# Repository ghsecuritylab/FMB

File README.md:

master only for working parts
work branch for incompltele/inprogress parts

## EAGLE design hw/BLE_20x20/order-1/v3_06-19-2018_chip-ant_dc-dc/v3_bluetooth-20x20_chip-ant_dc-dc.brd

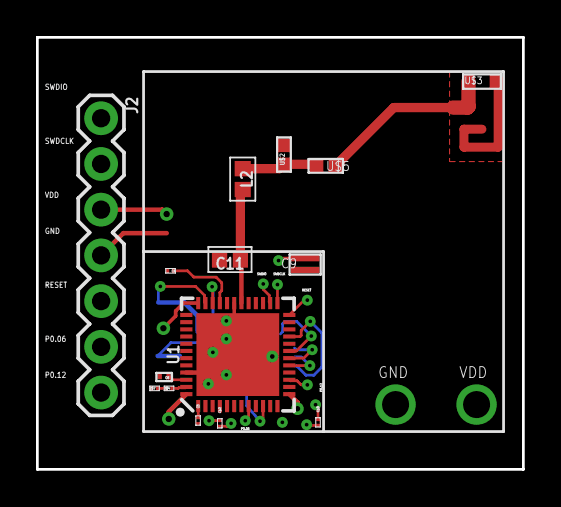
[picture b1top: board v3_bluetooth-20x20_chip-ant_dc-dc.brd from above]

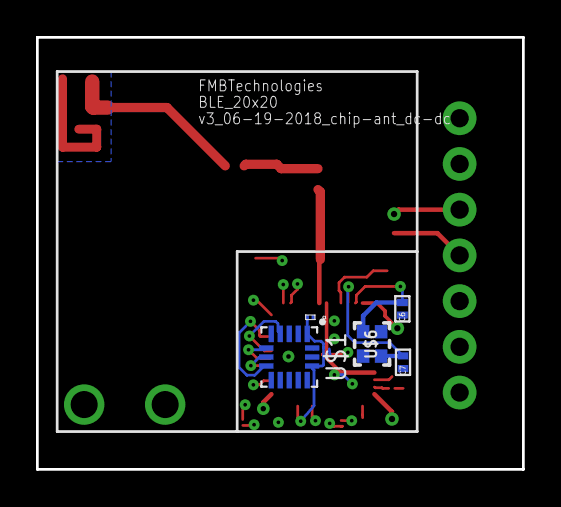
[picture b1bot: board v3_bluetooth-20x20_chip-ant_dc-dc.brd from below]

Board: 4 copper layers, 27.0 x 24.0 mm, 20 parts (5 on the bottom side), 22 nets.

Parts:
C1, C3, C10, C12: C0402X5R0G104M020BCCAP_0402-L; CAP_0402-L
C4: C0402C0G1C101J020BCCAP_0402-L; CAP_0402-L
C6, C7: GRM1555C1H6R0CA01D; CAPC1005X55N
C8: GRMMDXR60J105ME05D; CAPC0502X28N
C9: 4P7UFCAPACITOR4P7UFCAPACITOR; 4P7UFCAPACITOR
C11: 0.8pF; 0402
J2: header; 1X07
L2: 3.9nH; 0402
U1: NRF52832; QFN48-6X6MM
U$1: ADXL362; TFLGA-16/3.3MMX3.1MM
U$2: TUNINGINDUCTOR; 0402
U$3: 2450AT14A0100
U$4, U$7: INDUCTOR; 0402
U$5: 0402-1005
U$6: 32MHZCRYSTAL

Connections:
ADXL_POWER-QFAA: C1.2, U1.10, U$1.VDD/IO, U$1.VS
ANT-QFAA: C11.2, L2.1, U1.30
CS-QFAA: U1.21, U$1.CS
DEC1-QFAA: C3.1, U1.1
DEC3-QFAA: C4.1, U1.33
DEC4-QFAA: C8.1, U1.46
GND: C1.1, C3.2, C4.2, C6.1, C7.1, C8.2, C9.1, C10.1, C11.1, C12.1, J2.4, U1.31, U1.45, U1.EP, U$1.GND@1, U$1.GND@2, U$1.GND@3, U$2.2, U$7.1
MISO-QFAA: U1.17, U$1.MISO
MOSI-QFAA: U1.18, U$1.MOSI
unnamed: L2.2, U$2.1, U$5.2
unnamed: U$3.FEED, U$5.1
unnamed: U1.47, U$4.2
unnamed: U$4.1, U$7.2
P0.06-QFAA: J2.6, U1.8
P0.12-QFAA: J2.7, U1.15
RESET-QFAA: J2.5, U1.24
SCLK-QFAA: U1.19, U$1.SCLK
SWDCLK-QFAA: J2.2, U1.25
SWDIO-QFAA: J2.1, U1.26
VDD: C9.2, C10.2, C12.2, J2.3, U1.13, U1.36, U1.48
XC1-QFAA: C7.2, U1.34, U$6.1
XC2-QFAA: C6.2, U1.35, U$6.3

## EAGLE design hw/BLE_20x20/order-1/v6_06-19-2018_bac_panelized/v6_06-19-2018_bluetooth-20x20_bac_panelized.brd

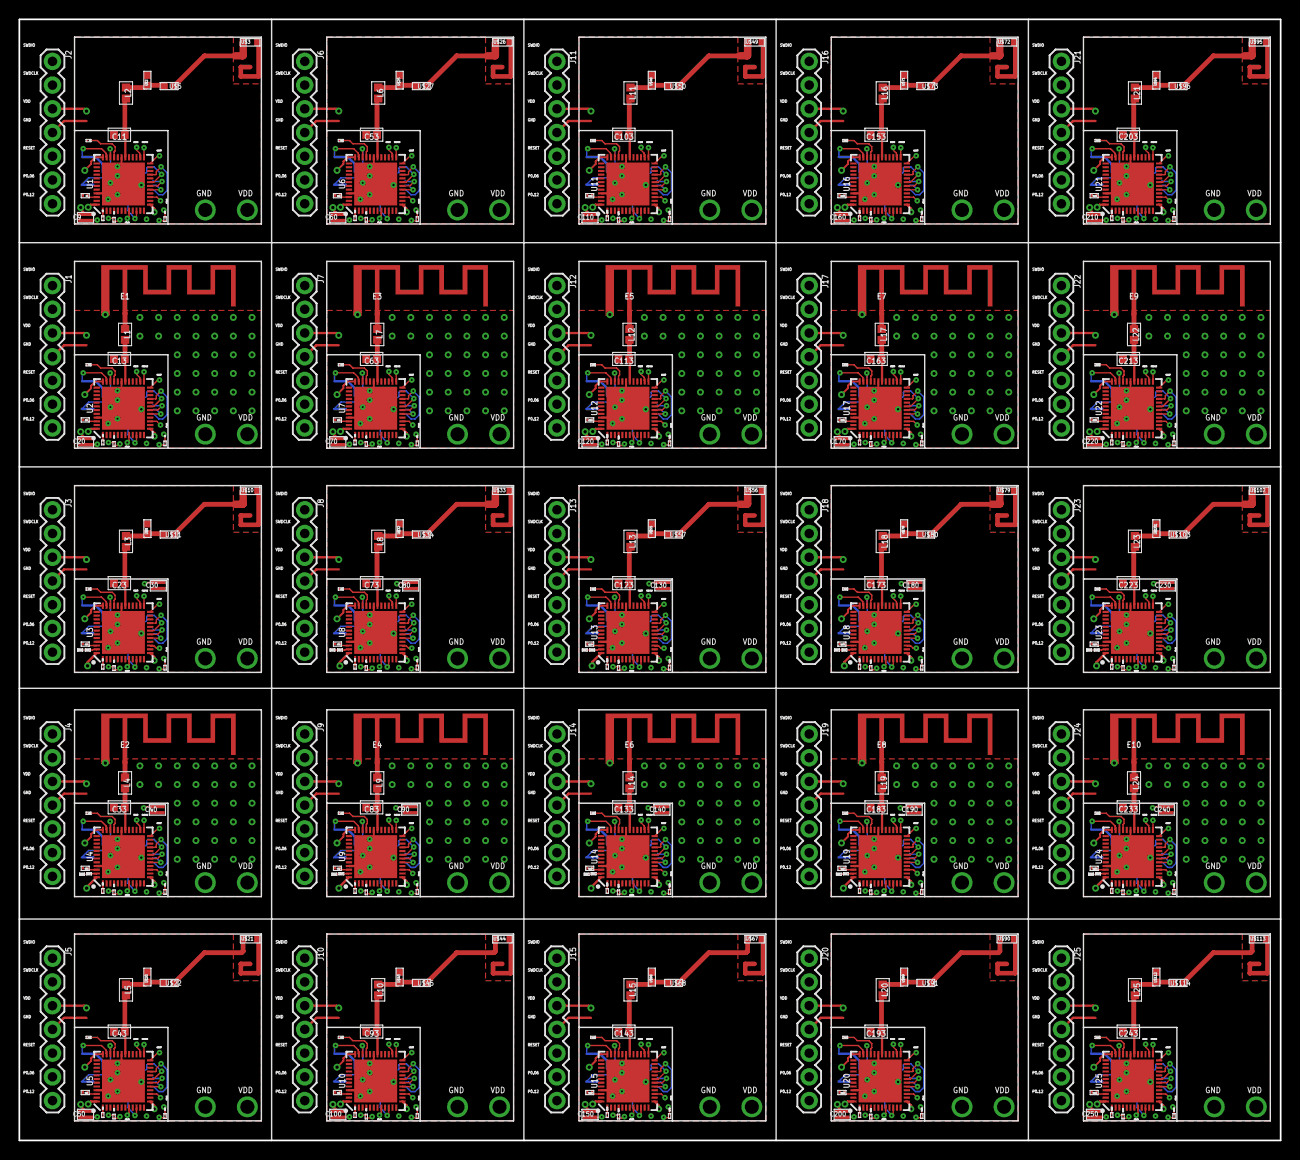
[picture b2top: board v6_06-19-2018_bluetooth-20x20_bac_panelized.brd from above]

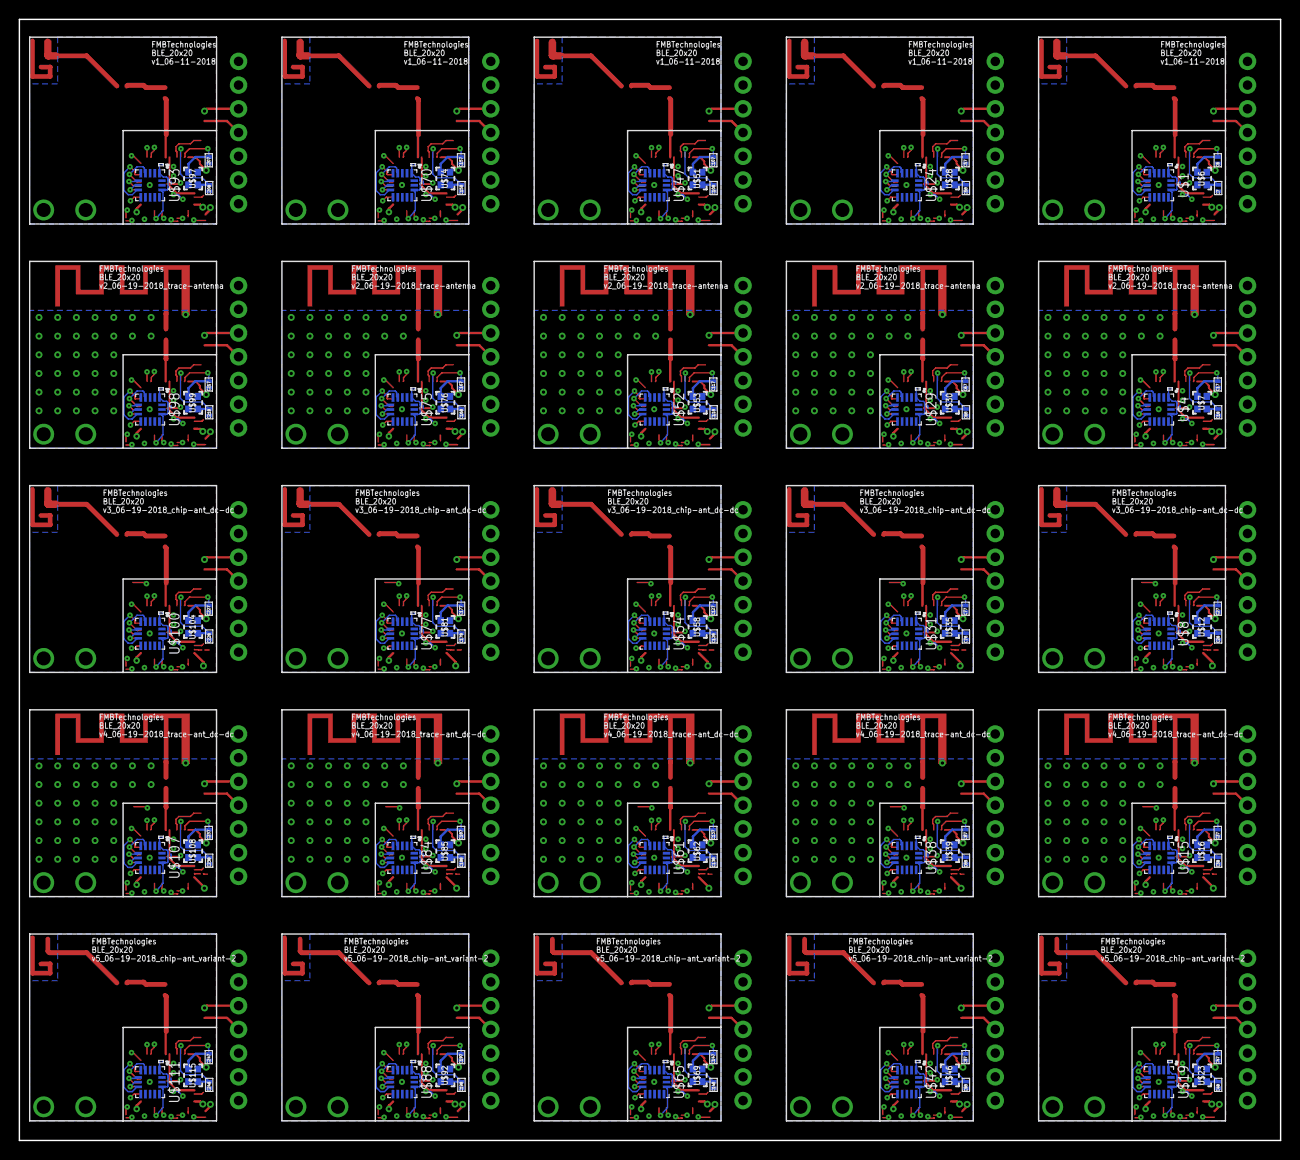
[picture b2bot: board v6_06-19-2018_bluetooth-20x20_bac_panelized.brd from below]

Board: 4 copper layers, 135.0 x 120.0 mm, 450 parts (125 on the bottom side), 510 nets.

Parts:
C1, C2, C3, C5, C10, C12, C14, C15, C21, C22, C24, C25, C31, C32, C34, C35, C41, C42, C44, C45, C51, C52, C54, C55, C61, C62, C64, C65, C71, C72, C74, C75, C81, C82, C84, C85, C91, C92, C94, C95, C101, C102, C104, C105, C111, C112, C114, C115, C121, C122, C124, C125, C131, C132, C134, C135, C141, C142, C144, C145, C151, C152, C154, C155, C161, C162, C164, C165, C171, C172, C174, C175, C181, C182, C184, C185, C191, C192, C194, C195, C201, C202, C204, C205, C211, C212, C214, C215, C221, C222, C224, C225, C231, C232, C234, C235, C241, C242, C244, C245: C0402X5R0G104M020BCCAP_0402-L; CAP_0402-L
C4, C16, C26, C36, C46, C56, C66, C76, C86, C96, C106, C116, C126, C136, C146, C156, C166, C176, C186, C196, C206, C216, C226, C236, C246: C0402C0G1C101J020BCCAP_0402-L; CAP_0402-L
C6, C7, C17, C18, C27, C28, C37, C38, C47, C48, C57, C58, C67, C68, C77, C78, C87, C88, C97, C98, C107, C108, C117, C118, C127, C128, C137, C138, C147, C148, C157, C158, C167, C168, C177, C178, C187, C188, C197, C198, C207, C208, C217, C218, C227, C228, C237, C238, C247, C248: GRM1555C1H6R0CA01D; CAPC1005X55N
C8, C19, C29, C39, C49, C59, C69, C79, C89, C99, C109, C119, C129, C139, C149, C159, C169, C179, C189, C199, C209, C219, C229, C239, C249: GRMMDXR60J105ME05D; CAPC0502X28N
C9, C20, C30, C40, C50, C60, C70, C80, C90, C100, C110, C120, C130, C140, C150, C160, C170, C180, C190, C200, C210, C220, C230, C240, C250: 4P7UFCAPACITOR4P7UFCAPACITOR; 4P7UFCAPACITOR
C11, C13, C23, C33, C43, C53, C63, C73, C83, C93, C103, C113, C123, C133, C143, C153, C163, C173, C183, C193, C203, C213, C223, C233, C243: 0.8pF; 0402
E1, E2, E3, E4, E5, E6, E7, E8, E9, E10: ANT; TRACE_ANTENNA_2.4GHZ_15.2MM
J1, J2, J3, J4, J5, J6, J7, J8, J9, J10, J11, J12, J13, J14, J15, J16, J17, J18, J19, J20, J21, J22, J23, J24, J25: header; 1X07
L1, L2, L3, L4, L5, L6, L7, L8, L9, L10, L11, L12, L13, L14, L15, L16, L17, L18, L19, L20, L21, L22, L23, L24, L25: 3.9nH; 0402
U1, U2, U3, U4, U5, U6, U7, U8, U9, U10, U11, U12, U13, U14, U15, U16, U17, U18, U19, U20, U21, U22, U23, U24, U25: NRF52832; QFN48-6X6MM
U$1, U$4, U$8, U$15, U$19, U$24, U$29, U$31, U$38, U$42, U$47, U$52, U$54, U$61, U$65, U$70, U$75, U$77, U$84, U$88, U$93, U$98, U$100, U$107, U$111: ADXL362; TFLGA-16/3.3MMX3.1MM
U$2, U$9, U$20, U$25, U$32, U$43, U$48, U$55, U$66, U$71, U$78, U$89, U$94, U$101, U$112: TUNINGINDUCTOR; 0402
U$3, U$10, U$21, U$26, U$33, U$44, U$49, U$56, U$67, U$72, U$79, U$90, U$95, U$102, U$113: 2450AT14A0100
U$5, U$11, U$22, U$27, U$34, U$45, U$50, U$57, U$68, U$73, U$80, U$91, U$96, U$103, U$114: 0402-1005
U$6, U$7, U$12, U$16, U$23, U$28, U$30, U$35, U$39, U$46, U$51, U$53, U$58, U$62, U$69, U$74, U$76, U$81, U$85, U$92, U$97, U$99, U$104, U$108, U$115: 32MHZCRYSTAL
U$13, U$14, U$17, U$18, U$36, U$37, U$40, U$41, U$59, U$60, U$63, U$64, U$82, U$83, U$86, U$87, U$105, U$106, U$109, U$110: INDUCTOR; 0402

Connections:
ADXL_POWER-QFAA: C1.2, U1.10, U$1.VDD/IO, U$1.VS
ADXL_POWER-QFAA1: C2.2, U2.10, U$4.VDD/IO, U$4.VS
ADXL_POWER-QFAA2: C21.2, U3.10, U$8.VDD/IO, U$8.VS
ADXL_POWER-QFAA3: C31.2, U4.10, U$15.VDD/IO, U$15.VS
ADXL_POWER-QFAA4: C41.2, U5.10, U$19.VDD/IO, U$19.VS
ADXL_POWER-QFAA5: C51.2, U6.10, U$24.VDD/IO, U$24.VS
ADXL_POWER-QFAA6: C61.2, U7.10, U$29.VDD/IO, U$29.VS
ADXL_POWER-QFAA7: C71.2, U8.10, U$31.VDD/IO, U$31.VS
ADXL_POWER-QFAA8: C81.2, U9.10, U$38.VDD/IO, U$38.VS
ADXL_POWER-QFAA9: C91.2, U10.10, U$42.VDD/IO, U$42.VS
ADXL_POWER-QFAA10: C101.2, U11.10, U$47.VDD/IO, U$47.VS
ADXL_POWER-QFAA11: C111.2, U12.10, U$52.VDD/IO, U$52.VS
ADXL_POWER-QFAA12: C121.2, U13.10, U$54.VDD/IO, U$54.VS
ADXL_POWER-QFAA13: C131.2, U14.10, U$61.VDD/IO, U$61.VS
ADXL_POWER-QFAA14: C141.2, U15.10, U$65.VDD/IO, U$65.VS
ADXL_POWER-QFAA15: C151.2, U16.10, U$70.VDD/IO, U$70.VS
ADXL_POWER-QFAA16: C161.2, U17.10, U$75.VDD/IO, U$75.VS
ADXL_POWER-QFAA17: C171.2, U18.10, U$77.VDD/IO, U$77.VS
ADXL_POWER-QFAA18: C181.2, U19.10, U$84.VDD/IO, U$84.VS
ADXL_POWER-QFAA19: C191.2, U20.10, U$88.VDD/IO, U$88.VS
ADXL_POWER-QFAA20: C201.2, U21.10, U$93.VDD/IO, U$93.VS
ADXL_POWER-QFAA21: C211.2, U22.10, U$98.VDD/IO, U$98.VS
ADXL_POWER-QFAA22: C221.2, U23.10, U$100.VDD/IO, U$100.VS
ADXL_POWER-QFAA23: C231.2, U24.10, U$107.VDD/IO, U$107.VS
ADXL_POWER-QFAA24: C241.2, U25.10, U$111.VDD/IO, U$111.VS
ANT-QFAA: C11.2, L2.1, U1.30
ANT-QFAA1: C13.2, L1.1, U2.30
ANT-QFAA2: C23.2, L3.1, U3.30
ANT-QFAA3: C33.2, L4.1, U4.30
ANT-QFAA4: C43.2, L5.1, U5.30
ANT-QFAA5: C53.2, L6.1, U6.30
ANT-QFAA6: C63.2, L7.1, U7.30
ANT-QFAA7: C73.2, L8.1, U8.30
ANT-QFAA8: C83.2, L9.1, U9.30
ANT-QFAA9: C93.2, L10.1, U10.30
ANT-QFAA10: C103.2, L11.1, U11.30
ANT-QFAA11: C113.2, L12.1, U12.30
ANT-QFAA12: C123.2, L13.1, U13.30
ANT-QFAA13: C133.2, L14.1, U14.30
ANT-QFAA14: C143.2, L15.1, U15.30
ANT-QFAA15: C153.2, L16.1, U16.30
ANT-QFAA16: C163.2, L17.1, U17.30
ANT-QFAA17: C173.2, L18.1, U18.30
ANT-QFAA18: C183.2, L19.1, U19.30
ANT-QFAA19: C193.2, L20.1, U20.30
ANT-QFAA20: C203.2, L21.1, U21.30
ANT-QFAA21: C213.2, L22.1, U22.30
ANT-QFAA22: C223.2, L23.1, U23.30
ANT-QFAA23: C233.2, L24.1, U24.30
ANT-QFAA24: C243.2, L25.1, U25.30
CS-QFAA: U1.21, U$1.CS
CS-QFAA1: U2.21, U$4.CS
CS-QFAA2: U3.21, U$8.CS
CS-QFAA3: U4.21, U$15.CS
CS-QFAA4: U5.21, U$19.CS
CS-QFAA5: U6.21, U$24.CS
CS-QFAA6: U7.21, U$29.CS
CS-QFAA7: U8.21, U$31.CS
CS-QFAA8: U9.21, U$38.CS
CS-QFAA9: U10.21, U$42.CS
CS-QFAA10: U11.21, U$47.CS
CS-QFAA11: U12.21, U$52.CS
CS-QFAA12: U13.21, U$54.CS
CS-QFAA13: U14.21, U$61.CS
CS-QFAA14: U15.21, U$65.CS
CS-QFAA15: U16.21, U$70.CS
CS-QFAA16: U17.21, U$75.CS
CS-QFAA17: U18.21, U$77.CS
CS-QFAA18: U19.21, U$84.CS
CS-QFAA19: U20.21, U$88.CS
CS-QFAA20: U21.21, U$93.CS
CS-QFAA21: U22.21, U$98.CS
CS-QFAA22: U23.21, U$100.CS
CS-QFAA23: U24.21, U$107.CS
CS-QFAA24: U25.21, U$111.CS
DEC1-QFAA: C3.1, U1.1
DEC1-QFAA1: C15.1, U2.1
DEC1-QFAA2: C25.1, U3.1
DEC1-QFAA3: C35.1, U4.1
DEC1-QFAA4: C45.1, U5.1
DEC1-QFAA5: C55.1, U6.1
DEC1-QFAA6: C65.1, U7.1
DEC1-QFAA7: C75.1, U8.1
DEC1-QFAA8: C85.1, U9.1
DEC1-QFAA9: C95.1, U10.1
DEC1-QFAA10: C105.1, U11.1
DEC1-QFAA11: C115.1, U12.1
DEC1-QFAA12: C125.1, U13.1
DEC1-QFAA13: C135.1, U14.1
DEC1-QFAA14: C145.1, U15.1
DEC1-QFAA15: C155.1, U16.1
DEC1-QFAA16: C165.1, U17.1
DEC1-QFAA17: C175.1, U18.1
DEC1-QFAA18: C185.1, U19.1
DEC1-QFAA19: C195.1, U20.1
DEC1-QFAA20: C205.1, U21.1
DEC1-QFAA21: C215.1, U22.1
DEC1-QFAA22: C225.1, U23.1
DEC1-QFAA23: C235.1, U24.1
DEC1-QFAA24: C245.1, U25.1
DEC3-QFAA: C4.1, U1.33
DEC3-QFAA1: C16.1, U2.33
DEC3-QFAA2: C26.1, U3.33
DEC3-QFAA3: C36.1, U4.33
DEC3-QFAA4: C46.1, U5.33
DEC3-QFAA5: C56.1, U6.33
DEC3-QFAA6: C66.1, U7.33
DEC3-QFAA7: C76.1, U8.33
DEC3-QFAA8: C86.1, U9.33
DEC3-QFAA9: C96.1, U10.33
DEC3-QFAA10: C106.1, U11.33
DEC3-QFAA11: C116.1, U12.33
DEC3-QFAA12: C126.1, U13.33
DEC3-QFAA13: C136.1, U14.33
DEC3-QFAA14: C146.1, U15.33
DEC3-QFAA15: C156.1, U16.33
DEC3-QFAA16: C166.1, U17.33
DEC3-QFAA17: C176.1, U18.33
DEC3-QFAA18: C186.1, U19.33
DEC3-QFAA19: C196.1, U20.33
DEC3-QFAA20: C206.1, U21.33
DEC3-QFAA21: C216.1, U22.33
DEC3-QFAA22: C226.1, U23.33
DEC3-QFAA23: C236.1, U24.33
DEC3-QFAA24: C246.1, U25.33
DEC4-QFAA: C8.1, U1.46
DEC4-QFAA1: C19.1, U2.46
DEC4-QFAA2: C29.1, U3.46
DEC4-QFAA3: C39.1, U4.46
DEC4-QFAA4: C49.1, U5.46
DEC4-QFAA5: C59.1, U6.46
DEC4-QFAA6: C69.1, U7.46
DEC4-QFAA7: C79.1, U8.46
DEC4-QFAA8: C89.1, U9.46
DEC4-QFAA9: C99.1, U10.46
DEC4-QFAA10: C109.1, U11.46
DEC4-QFAA11: C119.1, U12.46
DEC4-QFAA12: C129.1, U13.46
DEC4-QFAA13: C139.1, U14.46
DEC4-QFAA14: C149.1, U15.46
DEC4-QFAA15: C159.1, U16.46
DEC4-QFAA16: C169.1, U17.46
DEC4-QFAA17: C179.1, U18.46
DEC4-QFAA18: C189.1, U19.46
DEC4-QFAA19: C199.1, U20.46
DEC4-QFAA20: C209.1, U21.46
DEC4-QFAA21: C219.1, U22.46
DEC4-QFAA22: C229.1, U23.46
DEC4-QFAA23: C239.1, U24.46
DEC4-QFAA24: C249.1, U25.46
GND: C1.1, C3.2, C4.2, C6.1, C7.1, C8.2, C9.1, C10.1, C11.1, C12.1, J2.4, U1.31, U1.45, U1.EP, U$1.GND@1, U$1.GND@2, U$1.GND@3, U$2.2
GND1: C2.1, C5.1, C13.1, C14.1, C15.2, C16.2, C17.1, C18.1, C19.2, C20.1, E1.GND, J1.4, U2.31, U2.45, U2.EP, U$4.GND@1, U$4.GND@2, U$4.GND@3
GND2: C21.1, C22.1, C23.1, C24.1, C25.2, C26.2, C27.1, C28.1, C29.2, C30.1, J3.4, U3.31, U3.45, U3.EP, U$8.GND@1, U$8.GND@2, U$8.GND@3, U$9.2, U$14.1
GND3: C31.1, C32.1, C33.1, C34.1, C35.2, C36.2, C37.1, C38.1, C39.2, C40.1, E2.GND, J4.4, U4.31, U4.45, U4.EP, U$15.GND@1, U$15.GND@2, U$15.GND@3, U$18.1
GND4: C41.1, C42.1, C43.1, C44.1, C45.2, C46.2, C47.1, C48.1, C49.2, C50.1, J5.4, U5.31, U5.45, U5.EP, U$19.GND@1, U$19.GND@2, U$19.GND@3, U$20.2
GND5: C51.1, C52.1, C53.1, C54.1, C55.2, C56.2, C57.1, C58.1, C59.2, C60.1, J6.4, U6.31, U6.45, U6.EP, U$24.GND@1, U$24.GND@2, U$24.GND@3, U$25.2
GND6: C61.1, C62.1, C63.1, C64.1, C65.2, C66.2, C67.1, C68.1, C69.2, C70.1, E3.GND, J7.4, U7.31, U7.45, U7.EP, U$29.GND@1, U$29.GND@2, U$29.GND@3
GND7: C71.1, C72.1, C73.1, C74.1, C75.2, C76.2, C77.1, C78.1, C79.2, C80.1, J8.4, U8.31, U8.45, U8.EP, U$31.GND@1, U$31.GND@2, U$31.GND@3, U$32.2, U$37.1
GND8: C81.1, C82.1, C83.1, C84.1, C85.2, C86.2, C87.1, C88.1, C89.2, C90.1, E4.GND, J9.4, U9.31, U9.45, U9.EP, U$38.GND@1, U$38.GND@2, U$38.GND@3, U$41.1
GND9: C91.1, C92.1, C93.1, C94.1, C95.2, C96.2, C97.1, C98.1, C99.2, C100.1, J10.4, U10.31, U10.45, U10.EP, U$42.GND@1, U$42.GND@2, U$42.GND@3, U$43.2
GND10: C101.1, C102.1, C103.1, C104.1, C105.2, C106.2, C107.1, C108.1, C109.2, C110.1, J11.4, U11.31, U11.45, U11.EP, U$47.GND@1, U$47.GND@2, U$47.GND@3, U$48.2
GND11: C111.1, C112.1, C113.1, C114.1, C115.2, C116.2, C117.1, C118.1, C119.2, C120.1, E5.GND, J12.4, U12.31, U12.45, U12.EP, U$52.GND@1, U$52.GND@2, U$52.GND@3
GND12: C121.1, C122.1, C123.1, C124.1, C125.2, C126.2, C127.1, C128.1, C129.2, C130.1, J13.4, U13.31, U13.45, U13.EP, U$54.GND@1, U$54.GND@2, U$54.GND@3, U$55.2, U$60.1
GND13: C131.1, C132.1, C133.1, C134.1, C135.2, C136.2, C137.1, C138.1, C139.2, C140.1, E6.GND, J14.4, U14.31, U14.45, U14.EP, U$61.GND@1, U$61.GND@2, U$61.GND@3, U$64.1
GND14: C141.1, C142.1, C143.1, C144.1, C145.2, C146.2, C147.1, C148.1, C149.2, C150.1, J15.4, U15.31, U15.45, U15.EP, U$65.GND@1, U$65.GND@2, U$65.GND@3, U$66.2
GND15: C151.1, C152.1, C153.1, C154.1, C155.2, C156.2, C157.1, C158.1, C159.2, C160.1, J16.4, U16.31, U16.45, U16.EP, U$70.GND@1, U$70.GND@2, U$70.GND@3, U$71.2
GND16: C161.1, C162.1, C163.1, C164.1, C165.2, C166.2, C167.1, C168.1, C169.2, C170.1, E7.GND, J17.4, U17.31, U17.45, U17.EP, U$75.GND@1, U$75.GND@2, U$75.GND@3
GND17: C171.1, C172.1, C173.1, C174.1, C175.2, C176.2, C177.1, C178.1, C179.2, C180.1, J18.4, U18.31, U18.45, U18.EP, U$77.GND@1, U$77.GND@2, U$77.GND@3, U$78.2, U$83.1
GND18: C181.1, C182.1, C183.1, C184.1, C185.2, C186.2, C187.1, C188.1, C189.2, C190.1, E8.GND, J19.4, U19.31, U19.45, U19.EP, U$84.GND@1, U$84.GND@2, U$84.GND@3, U$87.1
GND19: C191.1, C192.1, C193.1, C194.1, C195.2, C196.2, C197.1, C198.1, C199.2, C200.1, J20.4, U20.31, U20.45, U20.EP, U$88.GND@1, U$88.GND@2, U$88.GND@3, U$89.2
GND20: C201.1, C202.1, C203.1, C204.1, C205.2, C206.2, C207.1, C208.1, C209.2, C210.1, J21.4, U21.31, U21.45, U21.EP, U$93.GND@1, U$93.GND@2, U$93.GND@3, U$94.2
GND21: C211.1, C212.1, C213.1, C214.1, C215.2, C216.2, C217.1, C218.1, C219.2, C220.1, E9.GND, J22.4, U22.31, U22.45, U22.EP, U$98.GND@1, U$98.GND@2, U$98.GND@3
GND22: C221.1, C222.1, C223.1, C224.1, C225.2, C226.2, C227.1, C228.1, C229.2, C230.1, J23.4, U23.31, U23.45, U23.EP, U$100.GND@1, U$100.GND@2, U$100.GND@3, U$101.2, U$106.1
GND23: C231.1, C232.1, C233.1, C234.1, C235.2, C236.2, C237.1, C238.1, C239.2, C240.1, E10.GND, J24.4, U24.31, U24.45, U24.EP, U$107.GND@1, U$107.GND@2, U$107.GND@3, U$110.1
GND24: C241.1, C242.1, C243.1, C244.1, C245.2, C246.2, C247.1, C248.1, C249.2, C250.1, J25.4, U25.31, U25.45, U25.EP, U$111.GND@1, U$111.GND@2, U$111.GND@3, U$112.2
MISO-QFAA: U1.17, U$1.MISO
MISO-QFAA1: U2.17, U$4.MISO
MISO-QFAA2: U3.17, U$8.MISO
MISO-QFAA3: U4.17, U$15.MISO
MISO-QFAA4: U5.17, U$19.MISO
MISO-QFAA5: U6.17, U$24.MISO
MISO-QFAA6: U7.17, U$29.MISO
MISO-QFAA7: U8.17, U$31.MISO
MISO-QFAA8: U9.17, U$38.MISO
MISO-QFAA9: U10.17, U$42.MISO
MISO-QFAA10: U11.17, U$47.MISO
MISO-QFAA11: U12.17, U$52.MISO
MISO-QFAA12: U13.17, U$54.MISO
MISO-QFAA13: U14.17, U$61.MISO
MISO-QFAA14: U15.17, U$65.MISO
MISO-QFAA15: U16.17, U$70.MISO
MISO-QFAA16: U17.17, U$75.MISO
MISO-QFAA17: U18.17, U$77.MISO
MISO-QFAA18: U19.17, U$84.MISO
MISO-QFAA19: U20.17, U$88.MISO
MISO-QFAA20: U21.17, U$93.MISO
MISO-QFAA21: U22.17, U$98.MISO
MISO-QFAA22: U23.17, U$100.MISO
MISO-QFAA23: U24.17, U$107.MISO
MISO-QFAA24: U25.17, U$111.MISO
MOSI-QFAA: U1.18, U$1.MOSI
MOSI-QFAA1: U2.18, U$4.MOSI
MOSI-QFAA2: U3.18, U$8.MOSI
MOSI-QFAA3: U4.18, U$15.MOSI
MOSI-QFAA4: U5.18, U$19.MOSI
MOSI-QFAA5: U6.18, U$24.MOSI
MOSI-QFAA6: U7.18, U$29.MOSI
MOSI-QFAA7: U8.18, U$31.MOSI
MOSI-QFAA8: U9.18, U$38.MOSI
MOSI-QFAA9: U10.18, U$42.MOSI
MOSI-QFAA10: U11.18, U$47.MOSI
MOSI-QFAA11: U12.18, U$52.MOSI
MOSI-QFAA12: U13.18, U$54.MOSI
MOSI-QFAA13: U14.18, U$61.MOSI
MOSI-QFAA14: U15.18, U$65.MOSI
MOSI-QFAA15: U16.18, U$70.MOSI
MOSI-QFAA16: U17.18, U$75.MOSI
MOSI-QFAA17: U18.18, U$77.MOSI
MOSI-QFAA18: U19.18, U$84.MOSI
MOSI-QFAA19: U20.18, U$88.MOSI
MOSI-QFAA20: U21.18, U$93.MOSI
MOSI-QFAA21: U22.18, U$98.MOSI
MOSI-QFAA22: U23.18, U$100.MOSI
MOSI-QFAA23: U24.18, U$107.MOSI
MOSI-QFAA24: U25.18, U$111.MOSI
unnamed: L2.2, U$2.1, U$5.2
unnamed: U$3.FEED, U$5.1
unnamed: E1.ANT, L1.2
unnamed: L3.2, U$9.1, U$11.2
unnamed: U$10.FEED, U$11.1
unnamed: U3.47, U$13.2
unnamed: U$13.1, U$14.2
unnamed: E2.ANT, L4.2
unnamed: U$17.1, U$18.2
unnamed: U4.47, U$17.2
unnamed: L5.2, U$20.1, U$22.2
unnamed: U$21.FEED, U$22.1
unnamed: L6.2, U$25.1, U$27.2
unnamed: U$26.FEED, U$27.1
unnamed: E3.ANT, L7.2
unnamed: L8.2, U$32.1, U$34.2
unnamed: U$33.FEED, U$34.1
unnamed: U8.47, U$36.2
unnamed: U$36.1, U$37.2
unnamed: E4.ANT, L9.2
unnamed: U$40.1, U$41.2
unnamed: U9.47, U$40.2
unnamed: L10.2, U$43.1, U$45.2
unnamed: U$44.FEED, U$45.1
unnamed: L11.2, U$48.1, U$50.2
unnamed: U$49.FEED, U$50.1
unnamed: E5.ANT, L12.2
unnamed: L13.2, U$55.1, U$57.2
unnamed: U$56.FEED, U$57.1
unnamed: U13.47, U$59.2
unnamed: U$59.1, U$60.2
unnamed: E6.ANT, L14.2
unnamed: U$63.1, U$64.2
unnamed: U14.47, U$63.2
unnamed: L15.2, U$66.1, U$68.2
unnamed: U$67.FEED, U$68.1
unnamed: L16.2, U$71.1, U$73.2
unnamed: U$72.FEED, U$73.1
unnamed: E7.ANT, L17.2
unnamed: L18.2, U$78.1, U$80.2
unnamed: U$79.FEED, U$80.1
unnamed: U18.47, U$82.2
unnamed: U$82.1, U$83.2
unnamed: E8.ANT, L19.2
unnamed: U$86.1, U$87.2
unnamed: U19.47, U$86.2
unnamed: L20.2, U$89.1, U$91.2
unnamed: U$90.FEED, U$91.1
unnamed: L21.2, U$94.1, U$96.2
unnamed: U$95.FEED, U$96.1
unnamed: E9.ANT, L22.2
unnamed: L23.2, U$101.1, U$103.2
unnamed: U$102.FEED, U$103.1
unnamed: U23.47, U$105.2
unnamed: U$105.1, U$106.2
unnamed: E10.ANT, L24.2
unnamed: U$109.1, U$110.2
unnamed: U24.47, U$109.2
unnamed: L25.2, U$112.1, U$114.2
unnamed: U$113.FEED, U$114.1
P0.06-QFAA: J2.6, U1.8
P0.06-QFAA1: J1.6, U2.8
P0.06-QFAA2: J3.6, U3.8
P0.06-QFAA3: J4.6, U4.8
P0.06-QFAA4: J5.6, U5.8
P0.06-QFAA5: J6.6, U6.8
P0.06-QFAA6: J7.6, U7.8
P0.06-QFAA7: J8.6, U8.8
P0.06-QFAA8: J9.6, U9.8
P0.06-QFAA9: J10.6, U10.8
P0.06-QFAA10: J11.6, U11.8
P0.06-QFAA11: J12.6, U12.8
P0.06-QFAA12: J13.6, U13.8
P0.06-QFAA13: J14.6, U14.8
P0.06-QFAA14: J15.6, U15.8
P0.06-QFAA15: J16.6, U16.8
P0.06-QFAA16: J17.6, U17.8
P0.06-QFAA17: J18.6, U18.8
P0.06-QFAA18: J19.6, U19.8
P0.06-QFAA19: J20.6, U20.8
P0.06-QFAA20: J21.6, U21.8
P0.06-QFAA21: J22.6, U22.8
P0.06-QFAA22: J23.6, U23.8
P0.06-QFAA23: J24.6, U24.8
P0.06-QFAA24: J25.6, U25.8
P0.12-QFAA: J2.7, U1.15
P0.12-QFAA1: J1.7, U2.15
P0.12-QFAA2: J3.7, U3.15
P0.12-QFAA3: J4.7, U4.15
P0.12-QFAA4: J5.7, U5.15
P0.12-QFAA5: J6.7, U6.15
P0.12-QFAA6: J7.7, U7.15
P0.12-QFAA7: J8.7, U8.15
P0.12-QFAA8: J9.7, U9.15
P0.12-QFAA9: J10.7, U10.15
P0.12-QFAA10: J11.7, U11.15
P0.12-QFAA11: J12.7, U12.15
P0.12-QFAA12: J13.7, U13.15
P0.12-QFAA13: J14.7, U14.15
P0.12-QFAA14: J15.7, U15.15
P0.12-QFAA15: J16.7, U16.15
P0.12-QFAA16: J17.7, U17.15
P0.12-QFAA17: J18.7, U18.15
P0.12-QFAA18: J19.7, U19.15
P0.12-QFAA19: J20.7, U20.15
P0.12-QFAA20: J21.7, U21.15
P0.12-QFAA21: J22.7, U22.15
P0.12-QFAA22: J23.7, U23.15
P0.12-QFAA23: J24.7, U24.15
P0.12-QFAA24: J25.7, U25.15
RESET-QFAA: J2.5, U1.24
RESET-QFAA1: J1.5, U2.24
RESET-QFAA2: J3.5, U3.24
RESET-QFAA3: J4.5, U4.24
RESET-QFAA4: J5.5, U5.24
RESET-QFAA5: J6.5, U6.24
RESET-QFAA6: J7.5, U7.24
RESET-QFAA7: J8.5, U8.24
RESET-QFAA8: J9.5, U9.24
RESET-QFAA9: J10.5, U10.24
RESET-QFAA10: J11.5, U11.24
RESET-QFAA11: J12.5, U12.24
RESET-QFAA12: J13.5, U13.24
RESET-QFAA13: J14.5, U14.24
RESET-QFAA14: J15.5, U15.24
RESET-QFAA15: J16.5, U16.24
RESET-QFAA16: J17.5, U17.24
RESET-QFAA17: J18.5, U18.24
RESET-QFAA18: J19.5, U19.24
RESET-QFAA19: J20.5, U20.24
RESET-QFAA20: J21.5, U21.24
RESET-QFAA21: J22.5, U22.24
RESET-QFAA22: J23.5, U23.24
RESET-QFAA23: J24.5, U24.24
RESET-QFAA24: J25.5, U25.24
SCLK-QFAA: U1.19, U$1.SCLK
SCLK-QFAA1: U2.19, U$4.SCLK
SCLK-QFAA2: U3.19, U$8.SCLK
SCLK-QFAA3: U4.19, U$15.SCLK
SCLK-QFAA4: U5.19, U$19.SCLK
SCLK-QFAA5: U6.19, U$24.SCLK
SCLK-QFAA6: U7.19, U$29.SCLK
SCLK-QFAA7: U8.19, U$31.SCLK
SCLK-QFAA8: U9.19, U$38.SCLK
SCLK-QFAA9: U10.19, U$42.SCLK
SCLK-QFAA10: U11.19, U$47.SCLK
SCLK-QFAA11: U12.19, U$52.SCLK
SCLK-QFAA12: U13.19, U$54.SCLK
SCLK-QFAA13: U14.19, U$61.SCLK
SCLK-QFAA14: U15.19, U$65.SCLK
SCLK-QFAA15: U16.19, U$70.SCLK
SCLK-QFAA16: U17.19, U$75.SCLK
SCLK-QFAA17: U18.19, U$77.SCLK
SCLK-QFAA18: U19.19, U$84.SCLK
SCLK-QFAA19: U20.19, U$88.SCLK
SCLK-QFAA20: U21.19, U$93.SCLK
SCLK-QFAA21: U22.19, U$98.SCLK
SCLK-QFAA22: U23.19, U$100.SCLK
SCLK-QFAA23: U24.19, U$107.SCLK
SCLK-QFAA24: U25.19, U$111.SCLK
SWDCLK-QFAA: J2.2, U1.25
SWDCLK-QFAA1: J1.2, U2.25
SWDCLK-QFAA2: J3.2, U3.25
SWDCLK-QFAA3: J4.2, U4.25
SWDCLK-QFAA4: J5.2, U5.25
SWDCLK-QFAA5: J6.2, U6.25
SWDCLK-QFAA6: J7.2, U7.25
SWDCLK-QFAA7: J8.2, U8.25
SWDCLK-QFAA8: J9.2, U9.25
SWDCLK-QFAA9: J10.2, U10.25
SWDCLK-QFAA10: J11.2, U11.25
SWDCLK-QFAA11: J12.2, U12.25
SWDCLK-QFAA12: J13.2, U13.25
SWDCLK-QFAA13: J14.2, U14.25
SWDCLK-QFAA14: J15.2, U15.25
SWDCLK-QFAA15: J16.2, U16.25
SWDCLK-QFAA16: J17.2, U17.25
SWDCLK-QFAA17: J18.2, U18.25
SWDCLK-QFAA18: J19.2, U19.25
SWDCLK-QFAA19: J20.2, U20.25
SWDCLK-QFAA20: J21.2, U21.25
SWDCLK-QFAA21: J22.2, U22.25
SWDCLK-QFAA22: J23.2, U23.25
SWDCLK-QFAA23: J24.2, U24.25
SWDCLK-QFAA24: J25.2, U25.25
SWDIO-QFAA: J2.1, U1.26
SWDIO-QFAA1: J1.1, U2.26
SWDIO-QFAA2: J3.1, U3.26
SWDIO-QFAA3: J4.1, U4.26
SWDIO-QFAA4: J5.1, U5.26
SWDIO-QFAA5: J6.1, U6.26
SWDIO-QFAA6: J7.1, U7.26
SWDIO-QFAA7: J8.1, U8.26
SWDIO-QFAA8: J9.1, U9.26
SWDIO-QFAA9: J10.1, U10.26
SWDIO-QFAA10: J11.1, U11.26
SWDIO-QFAA11: J12.1, U12.26
SWDIO-QFAA12: J13.1, U13.26
SWDIO-QFAA13: J14.1, U14.26
SWDIO-QFAA14: J15.1, U15.26
SWDIO-QFAA15: J16.1, U16.26
SWDIO-QFAA16: J17.1, U17.26
SWDIO-QFAA17: J18.1, U18.26
SWDIO-QFAA18: J19.1, U19.26
SWDIO-QFAA19: J20.1, U20.26
SWDIO-QFAA20: J21.1, U21.26
SWDIO-QFAA21: J22.1, U22.26
SWDIO-QFAA22: J23.1, U23.26
SWDIO-QFAA23: J24.1, U24.26
SWDIO-QFAA24: J25.1, U25.26
VDD: C9.2, C10.2, C12.2, J2.3, U1.13, U1.36, U1.48
VDD1: C5.2, C14.2, C20.2, J1.3, U2.13, U2.36, U2.48
VDD2: C22.2, C24.2, C30.2, J3.3, U3.13, U3.36, U3.48
VDD3: C32.2, C34.2, C40.2, J4.3, U4.13, U4.36, U4.48
VDD4: C42.2, C44.2, C50.2, J5.3, U5.13, U5.36, U5.48
VDD5: C52.2, C54.2, C60.2, J6.3, U6.13, U6.36, U6.48
VDD6: C62.2, C64.2, C70.2, J7.3, U7.13, U7.36, U7.48
VDD7: C72.2, C74.2, C80.2, J8.3, U8.13, U8.36, U8.48
VDD8: C82.2, C84.2, C90.2, J9.3, U9.13, U9.36, U9.48
VDD9: C92.2, C94.2, C100.2, J10.3, U10.13, U10.36, U10.48
VDD10: C102.2, C104.2, C110.2, J11.3, U11.13, U11.36, U11.48
VDD11: C112.2, C114.2, C120.2, J12.3, U12.13, U12.36, U12.48
VDD12: C122.2, C124.2, C130.2, J13.3, U13.13, U13.36, U13.48
VDD13: C132.2, C134.2, C140.2, J14.3, U14.13, U14.36, U14.48
VDD14: C142.2, C144.2, C150.2, J15.3, U15.13, U15.36, U15.48
VDD15: C152.2, C154.2, C160.2, J16.3, U16.13, U16.36, U16.48
VDD16: C162.2, C164.2, C170.2, J17.3, U17.13, U17.36, U17.48
VDD17: C172.2, C174.2, C180.2, J18.3, U18.13, U18.36, U18.48
VDD18: C182.2, C184.2, C190.2, J19.3, U19.13, U19.36, U19.48
VDD19: C192.2, C194.2, C200.2, J20.3, U20.13, U20.36, U20.48
VDD20: C202.2, C204.2, C210.2, J21.3, U21.13, U21.36, U21.48
VDD21: C212.2, C214.2, C220.2, J22.3, U22.13, U22.36, U22.48
VDD22: C222.2, C224.2, C230.2, J23.3, U23.13, U23.36, U23.48
VDD23: C232.2, C234.2, C240.2, J24.3, U24.13, U24.36, U24.48
VDD24: C242.2, C244.2, C250.2, J25.3, U25.13, U25.36, U25.48
XC1-QFAA: C7.2, U1.34, U$6.1
XC1-QFAA1: C18.2, U2.34, U$7.1
XC1-QFAA2: C28.2, U3.34, U$12.1
XC1-QFAA3: C38.2, U4.34, U$16.1
XC1-QFAA4: C48.2, U5.34, U$23.1
XC1-QFAA5: C58.2, U6.34, U$28.1
XC1-QFAA6: C68.2, U7.34, U$30.1
XC1-QFAA7: C78.2, U8.34, U$35.1
XC1-QFAA8: C88.2, U9.34, U$39.1
XC1-QFAA9: C98.2, U10.34, U$46.1
XC1-QFAA10: C108.2, U11.34, U$51.1
XC1-QFAA11: C118.2, U12.34, U$53.1
XC1-QFAA12: C128.2, U13.34, U$58.1
XC1-QFAA13: C138.2, U14.34, U$62.1
XC1-QFAA14: C148.2, U15.34, U$69.1
XC1-QFAA15: C158.2, U16.34, U$74.1
XC1-QFAA16: C168.2, U17.34, U$76.1
XC1-QFAA17: C178.2, U18.34, U$81.1
XC1-QFAA18: C188.2, U19.34, U$85.1
XC1-QFAA19: C198.2, U20.34, U$92.1
XC1-QFAA20: C208.2, U21.34, U$97.1
XC1-QFAA21: C218.2, U22.34, U$99.1
XC1-QFAA22: C228.2, U23.34, U$104.1
XC1-QFAA23: C238.2, U24.34, U$108.1
XC1-QFAA24: C248.2, U25.34, U$115.1
XC2-QFAA: C6.2, U1.35, U$6.3
XC2-QFAA1: C17.2, U2.35, U$7.3
XC2-QFAA2: C27.2, U3.35, U$12.3
XC2-QFAA3: C37.2, U4.35, U$16.3
XC2-QFAA4: C47.2, U5.35, U$23.3
XC2-QFAA5: C57.2, U6.35, U$28.3
XC2-QFAA6: C67.2, U7.35, U$30.3
XC2-QFAA7: C77.2, U8.35, U$35.3
XC2-QFAA8: C87.2, U9.35, U$39.3
XC2-QFAA9: C97.2, U10.35, U$46.3
XC2-QFAA10: C107.2, U11.35, U$51.3
XC2-QFAA11: C117.2, U12.35, U$53.3
XC2-QFAA12: C127.2, U13.35, U$58.3
XC2-QFAA13: C137.2, U14.35, U$62.3
XC2-QFAA14: C147.2, U15.35, U$69.3
XC2-QFAA15: C157.2, U16.35, U$74.3
XC2-QFAA16: C167.2, U17.35, U$76.3
XC2-QFAA17: C177.2, U18.35, U$81.3
XC2-QFAA18: C187.2, U19.35, U$85.3
XC2-QFAA19: C197.2, U20.35, U$92.3
XC2-QFAA20: C207.2, U21.35, U$97.3
XC2-QFAA21: C217.2, U22.35, U$99.3
XC2-QFAA22: C227.2, U23.35, U$104.3
XC2-QFAA23: C237.2, U24.35, U$108.3
XC2-QFAA24: C247.2, U25.35, U$115.3

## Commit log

2018-06-12 new rep for versioning
2018-06-12 rm a
2018-06-12 20x20 ble
2018-06-12 readme
2018-06-12 Ble 20x20
2018-06-12 configured flash nb project
2018-06-13 fixed makefile and sdk_config.h
2018-06-13 cleaned up code
2018-06-13 logic analyzer adxl
2018-06-13 logic analysis
2018-06-13 flash logic analysis
2018-06-14 adxl serial bluetooth, some logic analyer code, test data
2018-06-14 serial bluetooth and some data
2018-06-18 working on ble 20x20 completing airwires
2018-06-18 finished pcb, added 112 tsilk
2018-06-18 finished bluetooth, added 112 tsilk
2018-06-18 minor changes forgot to add bottom layer isolate 0.132
2018-06-18 exported gerbers
2018-06-19 removed gerber need to fixing antenna landing and tail
2018-06-19 fixed antenna layout and tail
2018-06-19 fixed isolate polygon
2018-06-19 gerber
2018-06-20 designed 5 variants with dc-dc one without increasing to 0.8mm before antenna, panelized 25x25 and exported gerbers
2018-06-24 before leave
2020-03-08 `vallen` is verified to be less than `len`, therefore, it can never be the case that `vallen >= len + sizeof(rhostname)`.
    This PR fixes the check so the `rhostname` array does not overflow.
    Reported-by: Github Security Lab <securitylab@github.com>

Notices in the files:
parts and their libraries:
SparkFun-Connectors: Licensing: Creative Commons ShareAlike 4.0 International - https://creativecommons.org/licenses/by-sa/4.0
